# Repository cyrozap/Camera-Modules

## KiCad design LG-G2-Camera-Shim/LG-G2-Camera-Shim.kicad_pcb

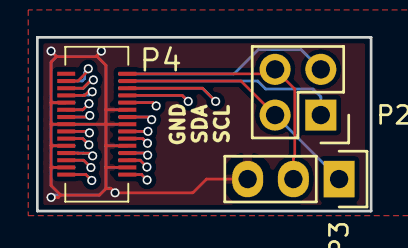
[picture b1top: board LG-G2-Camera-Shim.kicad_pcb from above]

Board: 2 copper layers, 18.5 x 9.7 mm, 4 parts (1 on the bottom side), 24 nets.

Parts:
P1: LG-G2-G3-Rear-Camera; GB042-30P
P2: CONN_02X02; Pin_Header_Straight_2x02
P3: CONN_01X03; Pin_Header_Straight_1x03
P4: LG-G2-G3-Rear-Camera; GB042-30S

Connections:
/+1V0_VREG_L3: P1.28, P4.28
/+1V8_13M_VCM: P1.3, P4.3
/+1V8_13M_VDDIO: P1.27, P4.27
/+2V7_13M_ANA: P1.16, P4.16
/+2V8_OIS_ANA: P1.15, P4.15
/+2V8_OIS_DIG: P1.4, P4.4
/CAM_MCLK: P1.24, P4.24
/CAM_RESET_N: P1.26, P4.26
/CAM_SCL: P2.2, P3.1, P4.29
/CAM_SDA: P2.4, P3.2, P4.30
/CLK_N: P1.13, P4.13
/CLK_P: P1.12, P4.12
/DATA0_N: P1.10, P4.10
/DATA0_P: P1.9, P4.9
/DATA1_N: P1.7, P4.7
/DATA1_P: P1.6, P4.6
/DATA2_N: P1.18, P4.18
/DATA2_P: P1.19, P4.19
/DATA3_N: P1.21, P4.21
/DATA3_P: P1.22, P4.22
/OIS_RESET_N: P1.2, P4.2
/PHONE_SCL: P1.29, P2.1
/PHONE_SDA: P1.30, P2.3
GND: P1.5, P1.8, P1.11, P1.14, P1.17, P1.20, P1.23, P1.25, P3.3, P4.5, P4.8, P4.11, P4.14, P4.17, P4.20, P4.23, P4.25

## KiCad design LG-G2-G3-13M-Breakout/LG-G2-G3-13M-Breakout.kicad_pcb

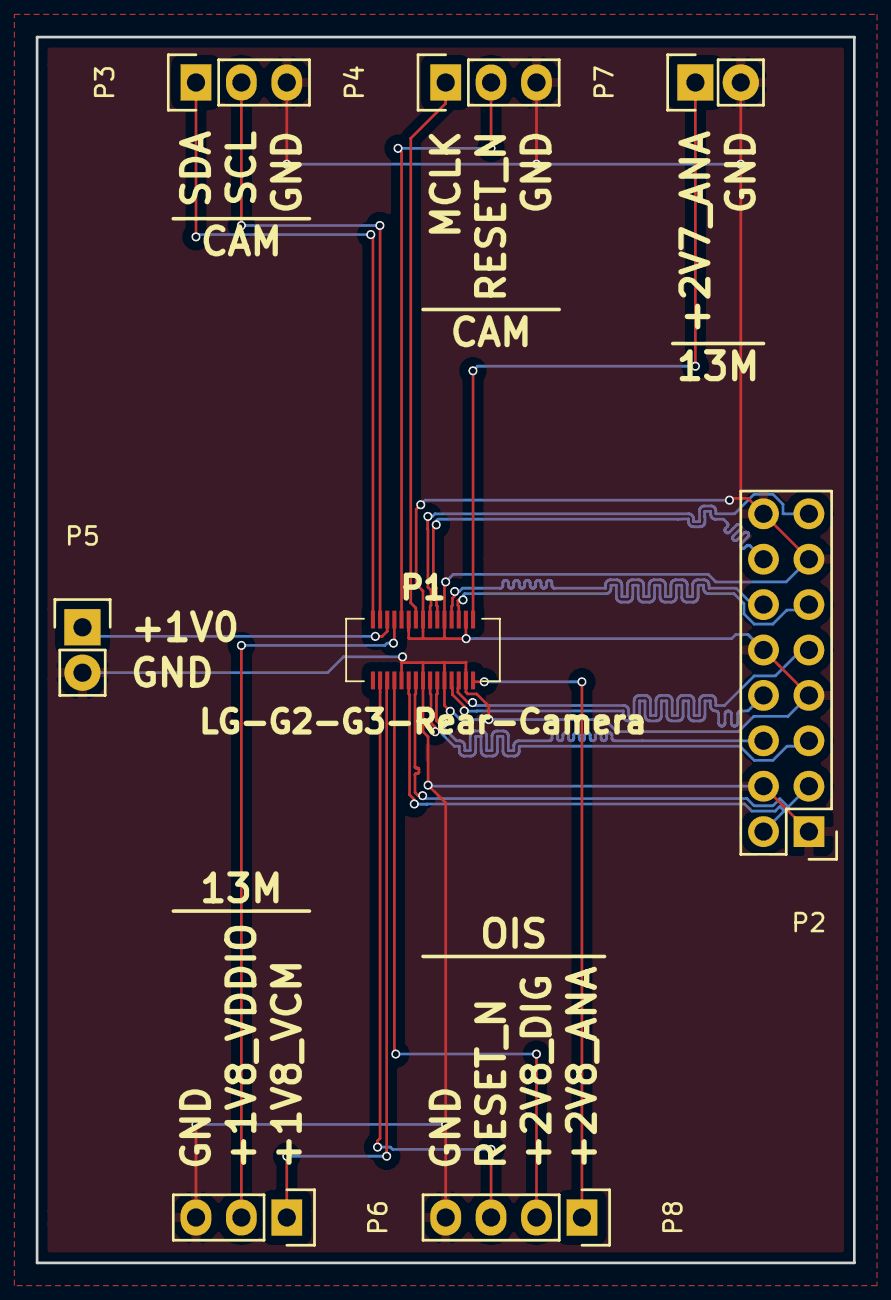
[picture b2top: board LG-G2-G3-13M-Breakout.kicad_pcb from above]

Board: 2 copper layers, 45.7 x 68.6 mm, 8 parts (0 on the bottom side), 22 nets.

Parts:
P1: LG-G2-G3-Rear-Camera; GB042-30S
P2: CONN_02X08; Pin_Header_Straight_2x08
P3, P4, P6: CONN_01X03; Pin_Header_Straight_1x03
P5, P7: CONN_01X02; Pin_Header_Straight_1x02
P8: CONN_01X04; Pin_Header_Straight_1x04

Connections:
/+1V0_VREG_L3: P1.28, P5.1
/+1V8_13M_VCM: P1.3, P6.1
/+1V8_13M_VDDIO: P1.27, P6.2
/+2V7_13M_ANA: P1.16, P7.1
/+2V8_OIS_ANA: P1.15, P8.1
/+2V8_OIS_DIG: P1.4, P8.2
/CAM_MCLK: P1.24, P4.1
/CAM_RESET_N: P1.26, P4.2
/CAM_SCL: P1.29, P3.2
/CAM_SDA: P1.30, P3.1
/CLK_N: P1.13, P2.9
/CLK_P: P1.12, P2.8
/DATA0_N: P1.10, P2.6
/DATA0_P: P1.9, P2.5
/DATA1_N: P1.7, P2.3
/DATA1_P: P1.6, P2.2
/DATA2_N: P1.18, P2.11
/DATA2_P: P1.19, P2.12
/DATA3_N: P1.21, P2.14
/DATA3_P: P1.22, P2.15
/OIS_RESET_N: P1.2, P8.3
GND: P1.5, P1.8, P1.11, P1.14, P1.17, P1.20, P1.23, P1.25, P2.1, P2.4, P2.7, P2.10, P2.13, P2.16, P3.3, P4.3, P5.2, P6.3, P7.2, P8.4

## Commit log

2016-02-23 Added .gitignore
2016-02-24 Added camera library and started breakout schematic
2016-02-24 Added cache libraries to .gitignore
2016-07-21 Finished the breakout schematic
2016-07-21 Finished designing the PCB
2016-07-21 Switched to the new component library
2016-07-21 Updated .gitignore
2016-07-21 Updated library to fix LG G2/G3 camera component pins
2016-07-22 Added shim to sniff LG G2 camera I2C communications
2017-04-17 Rename shim I2C nets
2017-04-17 Redraw shim for improved manufacturability
2017-04-18 Update plotting parameters for shim
